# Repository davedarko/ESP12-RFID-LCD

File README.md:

# ESP12-RFID-LCD
module to sandwich an 1.8 TFT SPI display and an MFRC522 module together
https://hackaday.io/project/8584-esp8266-rfid-reader

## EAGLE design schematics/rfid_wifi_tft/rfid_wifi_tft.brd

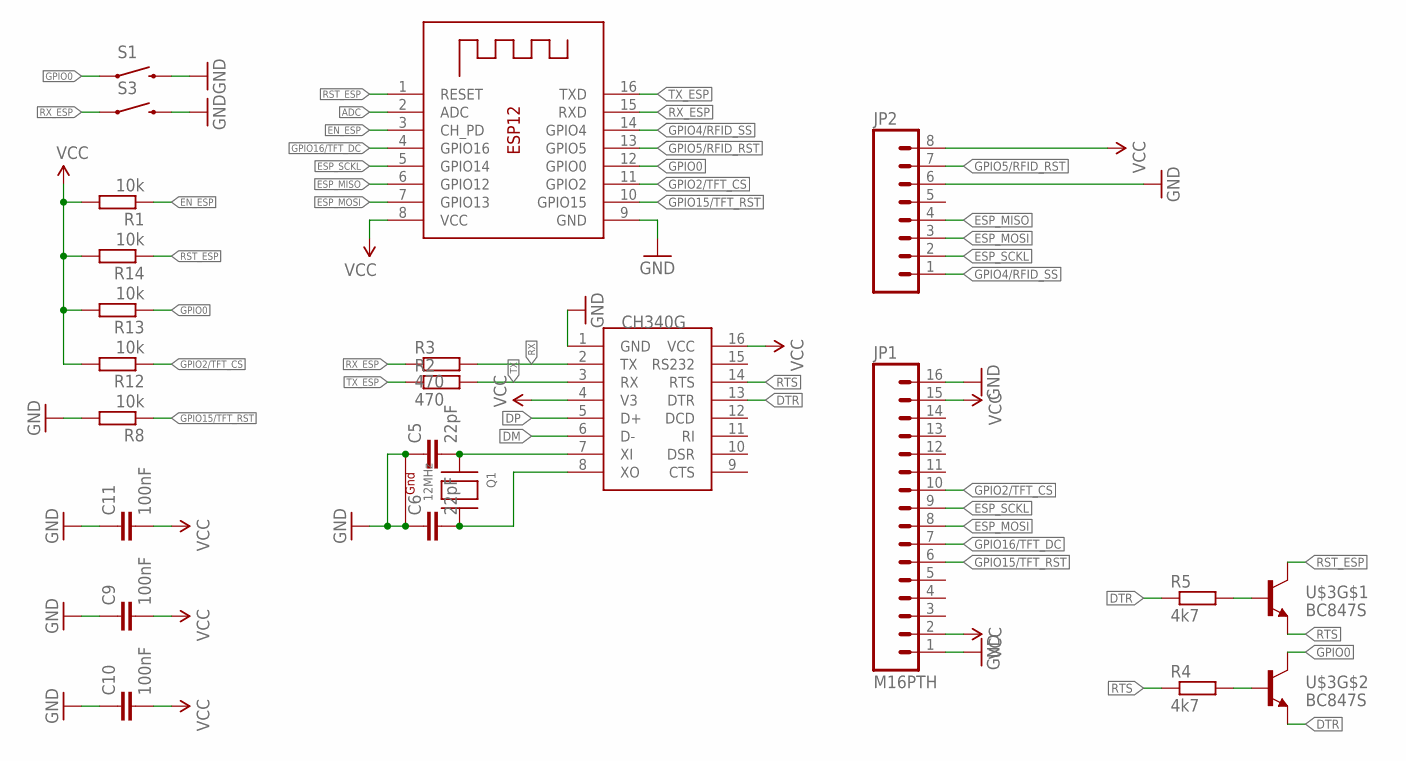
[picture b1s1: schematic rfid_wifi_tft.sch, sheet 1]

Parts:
C5, C6: 22pF; C0805
C9, C10, C11: 100nF; C0805
CH340G: CH340GCH340G; SOIC16
JP1: M16PTH; 1X16
JP2: M08; 1X08_ROUND
Q1: 12MHz; NX3225
R1, R8, R12, R13, R14: 10k; R0603
R2, R3: 470; R0603
R4, R5: 4k7; R0603
S1, S3: SWITCH-MOMENTARY-2-SMD-1101NE; TACTILE-SWITCH-1101NE
U$3: BC847S; SOT363
X1: ESP-12

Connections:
ADC: X1.2 (ADC); also elsewhere on the board
DM: CH340G.6 (D-); also elsewhere on the board
DP: CH340G.5 (D+); also elsewhere on the board
DTR: CH340G.13 (DTR), R5.1, U$3.1 (E)
EN_ESP: R1.1, X1.3 (CH_PD)
ESP_MISO: JP2.4, X1.6 (GPIO12)
ESP_MOSI: JP1.8, JP2.3, X1.7 (GPIO13)
ESP_SCKL: JP1.9, JP2.2, X1.5 (GPIO14)
GND: C5.1, C6.1, C9.1, C10.1, C11.1, CH340G.1 (GND), JP1.1, JP1.16, JP2.6, Q1.2 (G2), Q1.4 (G1), R8.2, S1.P$2 (2), S3.P$2 (2), X1.9 (GND); also elsewhere on the board
GPIO0: R13.1, S1.P$1 (1), U$3.6 (C), X1.12 (GPIO0)
GPIO2/TFT_CS: JP1.10, R12.1, X1.11 (GPIO2)
GPIO4/RFID_SS: JP2.1, X1.14 (GPIO4)
GPIO5/RFID_RST: JP2.7, X1.13 (GPIO5)
GPIO15/TFT_RST: JP1.6, R8.1, X1.10 (GPIO15)
GPIO16/TFT_DC: JP1.7, X1.4 (GPIO16)
unnamed: C5.2, CH340G.7 (XI), Q1.1 (X1)
unnamed: C6.2, CH340G.8 (XO), Q1.3 (X2)
unnamed: R5.2, U$3.5 (B)
unnamed: R4.2, U$3.2 (B)
RST_ESP: R14.1, U$3.3 (C), X1.1 (RESET)
RTS: CH340G.14 (RTS), R4.1, U$3.4 (E)
RX: CH340G.2 (TX), R3.2
RX_ESP: R3.1, S3.P$1 (1), X1.15 (RXD)
TX: CH340G.3 (RX), R2.2
TX_ESP: R2.1, X1.16 (TXD)
VCC: C9.2, C10.2, C11.2, CH340G.4 (V3), CH340G.16 (VCC), JP1.2, JP1.15, JP2.8, R1.2, R12.2, R13.2, R14.2, X1.8 (VCC); also elsewhere on the board

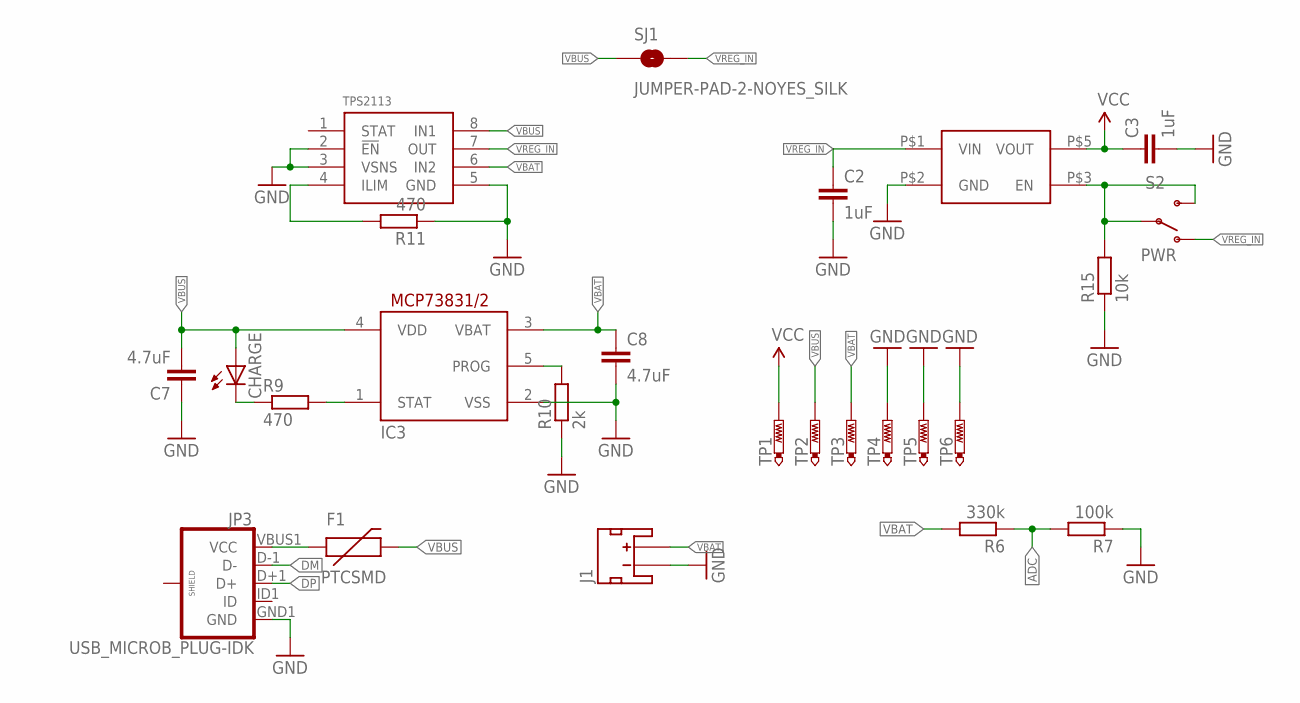
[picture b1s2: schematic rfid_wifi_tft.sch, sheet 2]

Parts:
C2, C3: 1uF; C0805
C7, C8: 4.7uF; C0805
CHARGE: LEDCHIP-LED0805; CHIP-LED0805
F1: PTCSMD; PTC-1206
IC3: MCP73831; SOT23-5L
J1: JST_2MM_MALE; JST-2-SMD
JP3: USB_MICROB_PLUG-IDK; USB-AB-MICRO-SMD_SLOT
R6: 330k; R0603
R7: 100k; R0603
R9, R11: 470; R0603
R10: 2k; R0603
R15: 10k; R0603
S2: PWR; SWITCH-SPST-SMD-A
SJ1: JUMPER-PAD-2-NOYES_SILK; PAD-JUMPER-2-NO_YES_SILK
TP1, TP2, TP3, TP4, TP5, TP6: PTR1B1,27; B1,27
U$4: TPS2113-PW; TEXAS-PW
U$9: AP2112KAP2112K; AP2112

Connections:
ADC: R6.1, R7.2; also elsewhere on the board
DM: JP3.D-1 (D-); also elsewhere on the board
DP: JP3.D+1 (D+); also elsewhere on the board
GND: C2.2, C3.2, C7.1, C8.2, IC3.2 (VSS), J1.1 (-), JP3.GND1 (GND), R7.1, R10.1, R11.1, R15.1, TP4.TP, TP5.TP, TP6.TP, U$4.2 (!EN), U$4.3 (VSNS), U$4.5 (GND), U$9.P$2 (GND); also elsewhere on the board
unnamed: IC3.1 (STAT), R9.2
unnamed: CHARGE.C, R9.1
unnamed: R11.2, U$4.4 (ILIM)
unnamed: IC3.5 (PROG), R10.2
VBAT: C8.1, IC3.3 (VBAT), J1.2 (+), R6.2, TP3.TP, U$4.6 (IN2)
VBUS: C7.2, CHARGE.A, F1.2, IC3.4 (VDD), SJ1.1, TP2.TP, U$4.8 (IN1)
VCC: C3.1, TP1.TP, U$9.P$5 (VOUT); also elsewhere on the board
VREG_EN: R15.2, S2.2, S2.3 (S), U$9.P$3 (EN)
VREG_IN: C2.1, S2.1 (O), SJ1.2, U$4.7 (OUT), U$9.P$1 (VIN)
VUSB: F1.1, JP3.VBUS1 (VCC)

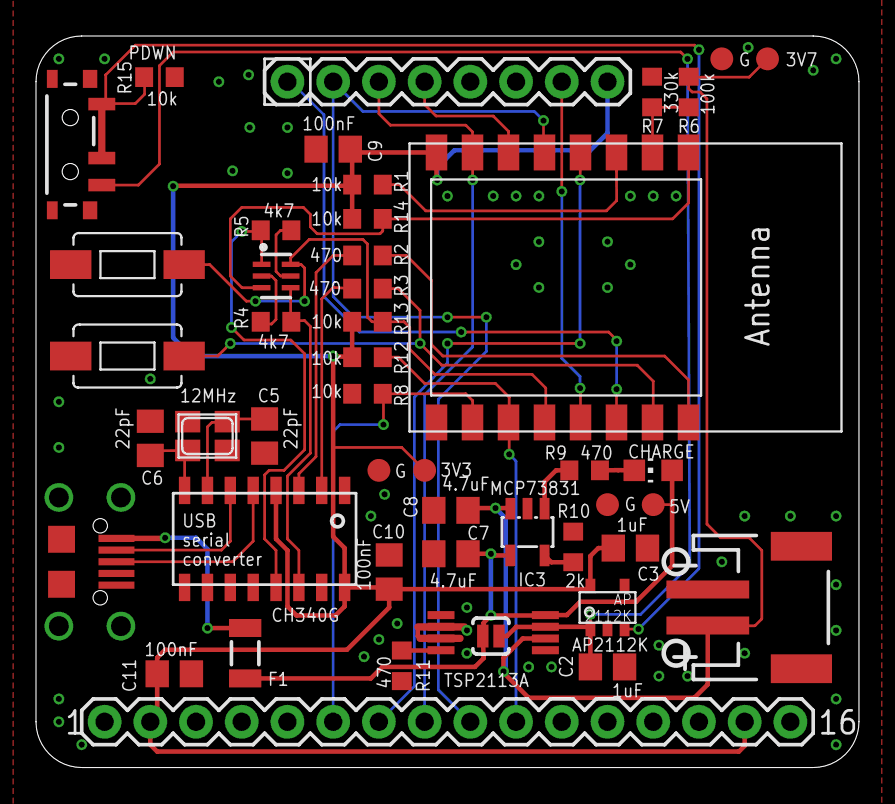
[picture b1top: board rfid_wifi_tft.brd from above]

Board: 2 copper layers, 45.7 x 40.6 mm, 49 parts (1 on the bottom side), 35 nets.

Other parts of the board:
U$1: DAVEDARKO_GOLD
U$2: DAVEDARKO2_LOGO

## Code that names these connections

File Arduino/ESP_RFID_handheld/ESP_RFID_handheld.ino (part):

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
/*
	12, 13, 14 are used for SPI,
	TFT_RST could be freed by connecting it to the ESP reset pin
*/
#define BTN_UP       0
#define BTN_DN       3
#define RFID_SS      5
#define RFID_RST     4
#define TFT_CS       2
#define TFT_DC      16
#define TFT_RST     15

MFRC522 mfrc522(RFID_SS, RFID_RST);
Adafruit_ST7735 tft_display = Adafruit_ST7735(TFT_CS, TFT_DC, TFT_RST);
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
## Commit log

2018-01-21 schematics and pcb design files
2018-10-18 added sketch
2018-10-18 added schematic revision
    fixed faulty enable pin wiring
2018-10-18 added hackadayio link to read me
2018-10-19 just styling

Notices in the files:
parts and their libraries:
SparkFun-Connectors: Licensing: Creative Commons ShareAlike 4.0 International - https://creativecommons.org/licenses/by-sa/4.0
